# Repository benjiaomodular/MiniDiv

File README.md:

# MiniDiv
[![CC BY-SA 4.0][cc-by-sa-shield]][cc-by-sa]

A simple clock divider based on [HAGIWO's  design](https://note.com/solder_state/n/n7979cda44dcb).

## Schematics

Project sponsored by [PCBWay](https://pcbway.com).

See my full docs on my website: https://benjiaomodular.com/post/2024-11-22-minidiv-pcb/

## Versions
#### v0.3 - Fixed LED clearance issue
- To address LED clearance issues, I moved the LEDs to be mounted to the back, facing down, such that the LED shines through a hole on the board. 

#### v0.2 - Initial release
- First working version
- ISSUE: The LEDs were preventing the jacks from going in completly. The module still works but it might cause problems in the future.

## License

This work is licensed under a
[Creative Commons Attribution-ShareAlike 4.0 International License][cc-by-sa].

[![CC BY-SA 4.0][cc-by-sa-image]][cc-by-sa]

[cc-by-sa]: http://creativecommons.org/licenses/by-sa/4.0/
[cc-by-sa-image]: https://licensebuttons.net/l/by-sa/4.0/88x31.png
[cc-by-sa-shield]: https://img.shields.io/badge/License-CC%20BY--SA%204.0-lightgrey.svg

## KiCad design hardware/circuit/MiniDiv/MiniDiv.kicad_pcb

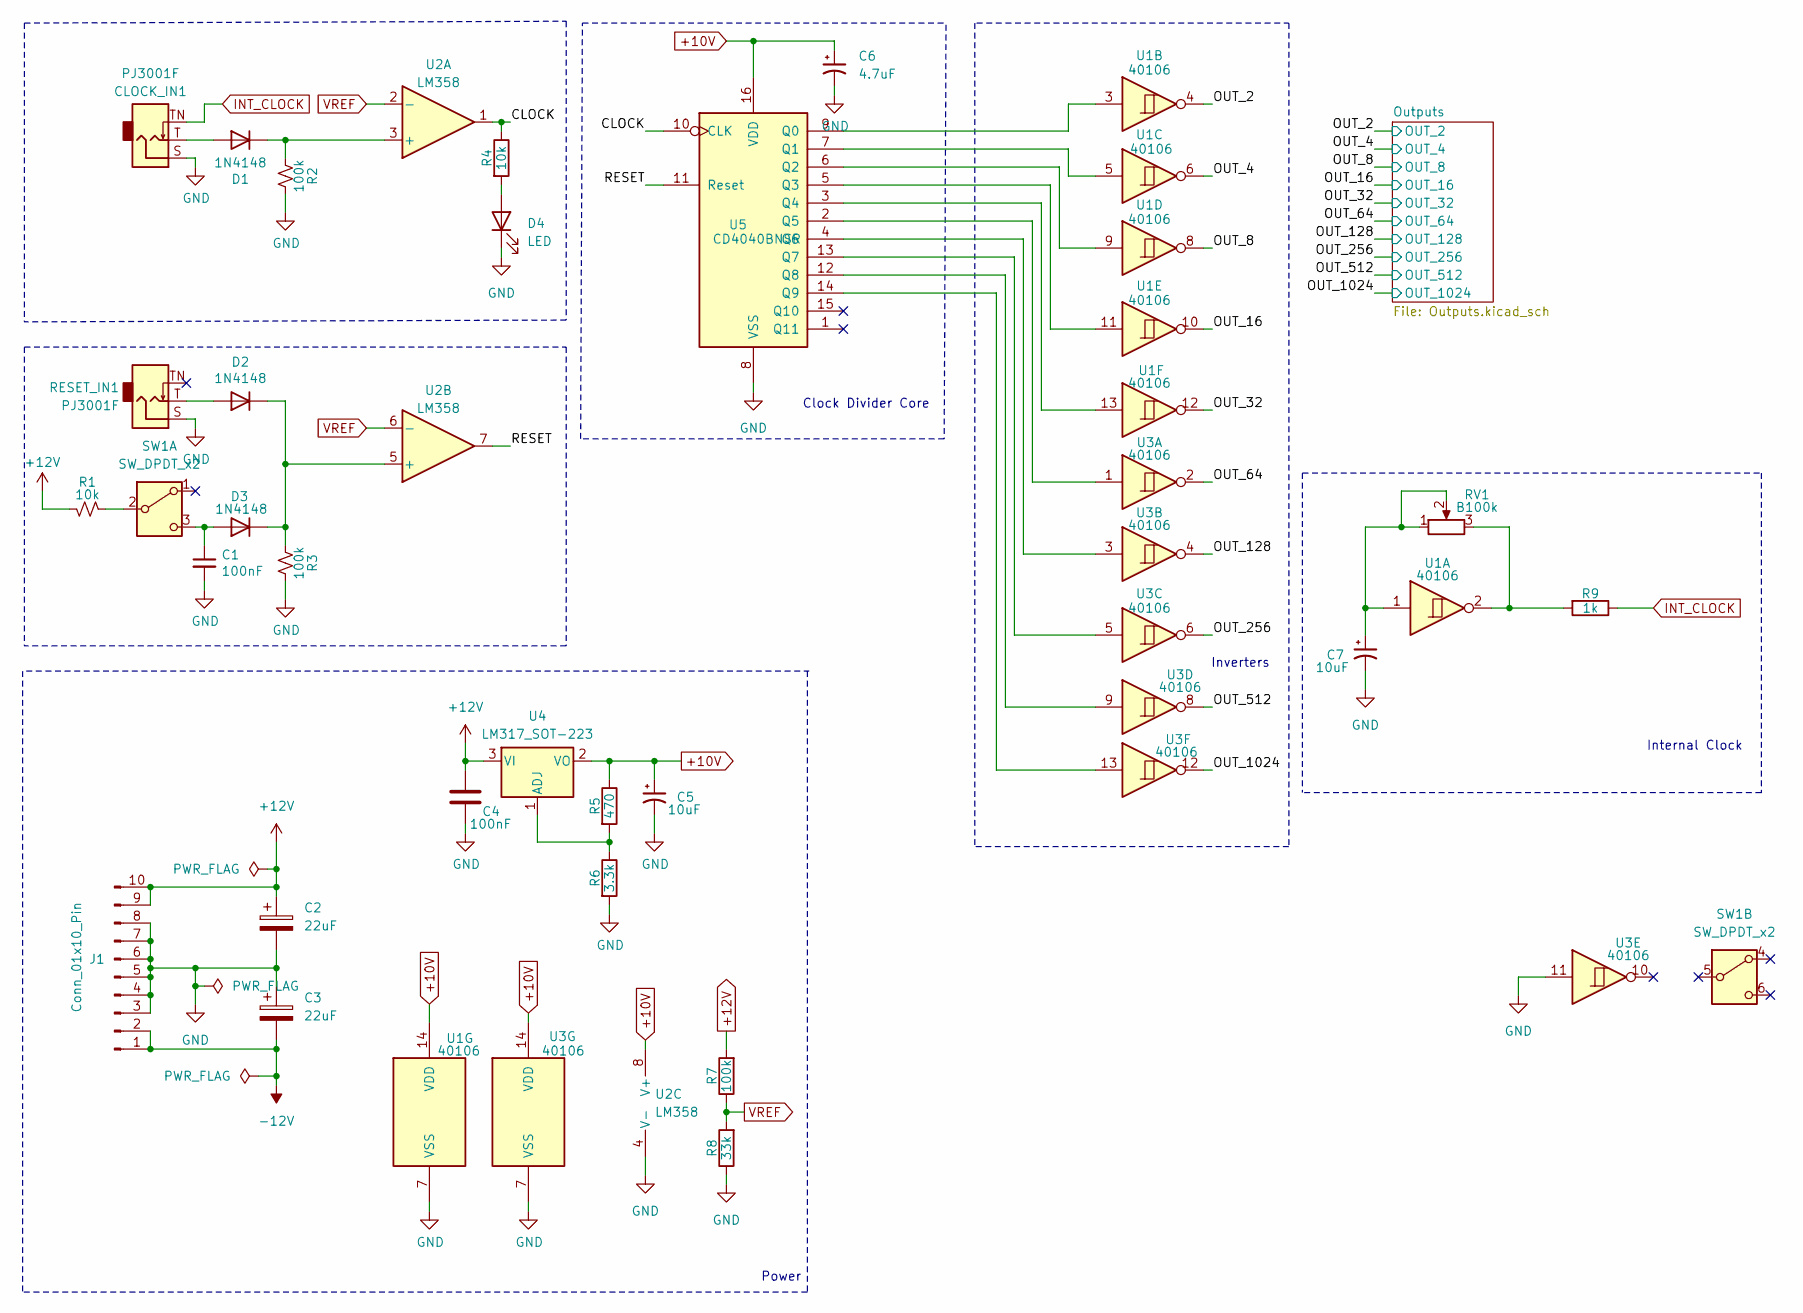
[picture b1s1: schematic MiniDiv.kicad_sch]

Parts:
C1: 100nF; C_0603_1608Metric_Pad1.08x0.95mm_HandSolder; Part # CC0805KRX7R9BB104
C2, C3: 22uF; CP_Elec_4x3.9; Part # EEE-FT1V220AR
C4: 100nF; C_0603_1608Metric_Pad1.08x0.95mm_HandSolder; Mfg # CC0603KRX7R8BB334; LCSC Part # C107070
C5, C7: 10uF; C_0805_2012Metric_Pad1.18x1.45mm_HandSolder; Part # TMK212BBJ106KG8T
C6: 4.7uF; C_0805_2012Metric_Pad1.18x1.45mm_HandSolder; Part # VJ0805G475KXQTW1BC
CLOCK_IN1: PJ3001F; AudioJack_3.5mm; Part # PJ-3001F
D1, D2, D3: 1N4148; D_SOD-123; Part # 1N4148WQ-7-F
D4: LED; LED_D3.0mm; Part # LED 3mm Orange
J1: Conn_01x10_Pin; Header_IDC2x05_NoArrow; Part # X9555WV-2X05-6TV01
R1, R4: 10k; R_0603_1608Metric_Pad0.98x0.95mm_HandSolder; Part # AC0603FR-0710KL
R2, R3, R7: 100k; R_0603_1608Metric_Pad0.98x0.95mm_HandSolder; Part # RC0603FR-07100KL
R5: 470; R_0603_1608Metric_Pad0.98x0.95mm_HandSolder; Part # RC0603FR-7W470RL
R6: 3.3k; R_0603_1608Metric_Pad0.98x0.95mm_HandSolder; Part # RC0603FR-7W3K3L
R8: 33k; R_0603_1608Metric_Pad0.98x0.95mm_HandSolder; Part # CR0603-FX-3302ELF
R9: 1k; R_0603_1608Metric_Pad0.98x0.95mm_HandSolder; Part # RC0603FR-071KL
RESET_IN1: PJ3001F; AudioJack_3.5mm; Part # PJ-3001F
RV1: B100k; Potentiometer_RV09; Part # RV09AF-40-20K-B100K
SW1: SW_DPDT_x2; Button_KFC7x7; Part # KFC7x7 Momentary
U1, U3: 40106; SOIC-14_3.9x8.7mm_P1.27mm; Part # Texas Instruments
U2: LM358; SOIC-8_5.23x5.23mm_P1.27mm; Part # Texas Instruments
U4: LM317_SOT-223; SOT-223-3_TabPin2; Part # Texas Instruments
U5: CD4040BNSR; SOIC-16W_5.3x10.2mm_P1.27mm; Part # Texas Instruments

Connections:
+10V: C5.1, C6.1, R5.1, U1.14 (VDD), U2.8 (V+), U3.14 (VDD), U4.2 (VO), U5.16 (VDD)
+12V: C2.1, C4.1, J1.9, J1.10, R1.1, R7.2, U4.3 (VI)
-12V: C3.2, J1.1, J1.2
/CLOCK: R4.1, U2.1, U5.10 (CLK)
/OUT_2: U1.4; also elsewhere on the board
/OUT_4: U1.6; also elsewhere on the board
/OUT_8: U1.8; also elsewhere on the board
/OUT_16: U1.10; also elsewhere on the board
/OUT_32: U1.12; also elsewhere on the board
/OUT_64: U3.2; also elsewhere on the board
/OUT_128: U3.4; also elsewhere on the board
/OUT_256: U3.6; also elsewhere on the board
/OUT_512: U3.8; also elsewhere on the board
/OUT_1024: U3.12; also elsewhere on the board
/RESET: U2.7, U5.11 (Reset)
GND: C1.2, C2.2, C3.1, C4.2, C5.2, C6.2, C7.2, CLOCK_IN1.S, D4.1 (K), J1.3, J1.4, J1.5, J1.6, J1.7, J1.8, R2.1, R3.1, R6.2, R8.1, RESET_IN1.S, U1.7 (VSS), U2.4 (V-), U3.7 (VSS), U3.11, U5.8 (VSS); also elsewhere on the board
INT_CLOCK: CLOCK_IN1.TN, R9.1
unnamed: C7.1, RV1.1, RV1.2, U1.1
unnamed: CLOCK_IN1.T, D1.2 (A)
unnamed: D1.1 (K), R2.2, U2.3 (+)
unnamed: D2.2 (A), RESET_IN1.T
unnamed: D2.1 (K), D3.1 (K), R3.2, U2.5 (+)
unnamed: C1.1, D3.2 (A), SW1.3 (C)
unnamed: D4.2 (A), R4.2
unnamed: R9.2, RV1.3, U1.2
unnamed: R1.2, SW1.2 (B)
unnamed: R5.2, R6.1, U4.1 (ADJ)
unnamed: U1.3, U5.9 (Q0)
unnamed: U1.5, U5.7 (Q1)
unnamed: U1.9, U5.6 (Q2)
unnamed: U1.11, U5.5 (Q3)
unnamed: U1.13, U5.3 (Q4)
unnamed: U3.1, U5.2 (Q5)
unnamed: U3.3, U5.4 (Q6)
unnamed: U3.5, U5.13 (Q7)
unnamed: U3.9, U5.12 (Q8)
unnamed: U3.13, U5.14 (Q9)
VREF: R7.1, R8.2, U2.2 (-), U2.6 (-)

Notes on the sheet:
Internal Clock
Clock Divider Core
Power
Inverters

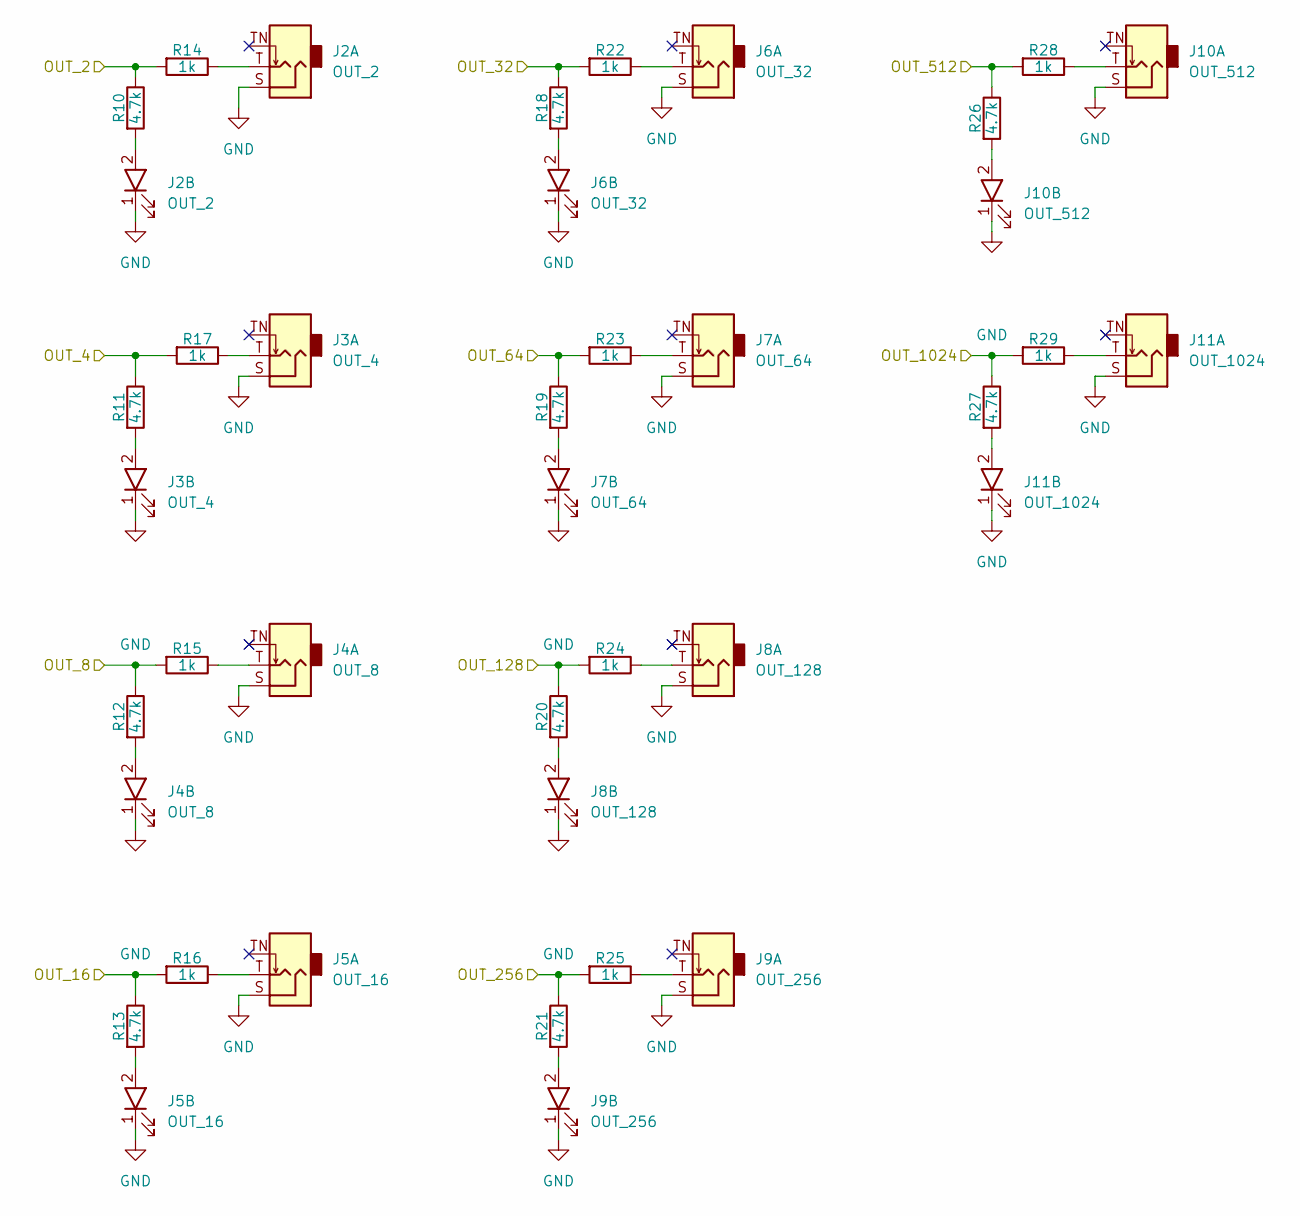
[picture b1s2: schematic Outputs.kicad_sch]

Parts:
J2: OUT_2; AudioJack_PJ3001F_0805LED
J3: OUT_4; AudioJack_PJ3001F_0805LED
J4: OUT_8; AudioJack_PJ3001F_0805LED
J5: OUT_16; AudioJack_PJ3001F_0805LED
J6: OUT_32; AudioJack_PJ3001F_0805LED
J7: OUT_64; AudioJack_PJ3001F_0805LED
J8: OUT_128; AudioJack_PJ3001F_0805LED
J9: OUT_256; AudioJack_PJ3001F_0805LED
J10: OUT_512; AudioJack_PJ3001F_0805LED
J11: OUT_1024; AudioJack_PJ3001F_0805LED
R10, R11, R12, R13, R18, R19, R20, R21, R26, R27: 4.7k; R_0603_1608Metric_Pad0.98x0.95mm_HandSolder; Part # RC0603FR-074K7L
R14, R15, R16, R17, R22, R23, R24, R25, R28, R29: 1k; R_0603_1608Metric_Pad0.98x0.95mm_HandSolder; Part # RC0603FR-071KL

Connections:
/OUT_2: R10.1, R14.2; also elsewhere on the board
/OUT_4: R11.1, R17.2; also elsewhere on the board
/OUT_8: R12.1, R15.2; also elsewhere on the board
/OUT_16: R13.1, R16.2; also elsewhere on the board
/OUT_32: R18.1, R22.2; also elsewhere on the board
/OUT_64: R19.1, R23.2; also elsewhere on the board
/OUT_128: R20.1, R24.2; also elsewhere on the board
/OUT_256: R21.1, R25.2; also elsewhere on the board
/OUT_512: R26.1, R28.2; also elsewhere on the board
/OUT_1024: R27.1, R29.2; also elsewhere on the board
GND: J2.1, J2.S, J3.1, J3.S, J4.1, J4.S, J5.1, J5.S, J6.1, J6.S, J7.1, J7.S, J8.1, J8.S, J9.1, J9.S, J10.1, J10.S, J11.1, J11.S; also elsewhere on the board
unnamed: J2.2, R10.2
unnamed: J2.T, R14.1
unnamed: J3.2, R11.2
unnamed: J3.T, R17.1
unnamed: J4.2, R12.2
unnamed: J4.T, R15.1
unnamed: J5.2, R13.2
unnamed: J5.T, R16.1
unnamed: J6.2, R18.2
unnamed: J6.T, R22.1
unnamed: J7.2, R19.2
unnamed: J7.T, R23.1
unnamed: J8.2, R20.2
unnamed: J8.T, R24.1
unnamed: J9.2, R21.2
unnamed: J9.T, R25.1
unnamed: J10.2, R26.2
unnamed: J10.T, R28.1
unnamed: J11.2, R27.2
unnamed: J11.T, R29.1

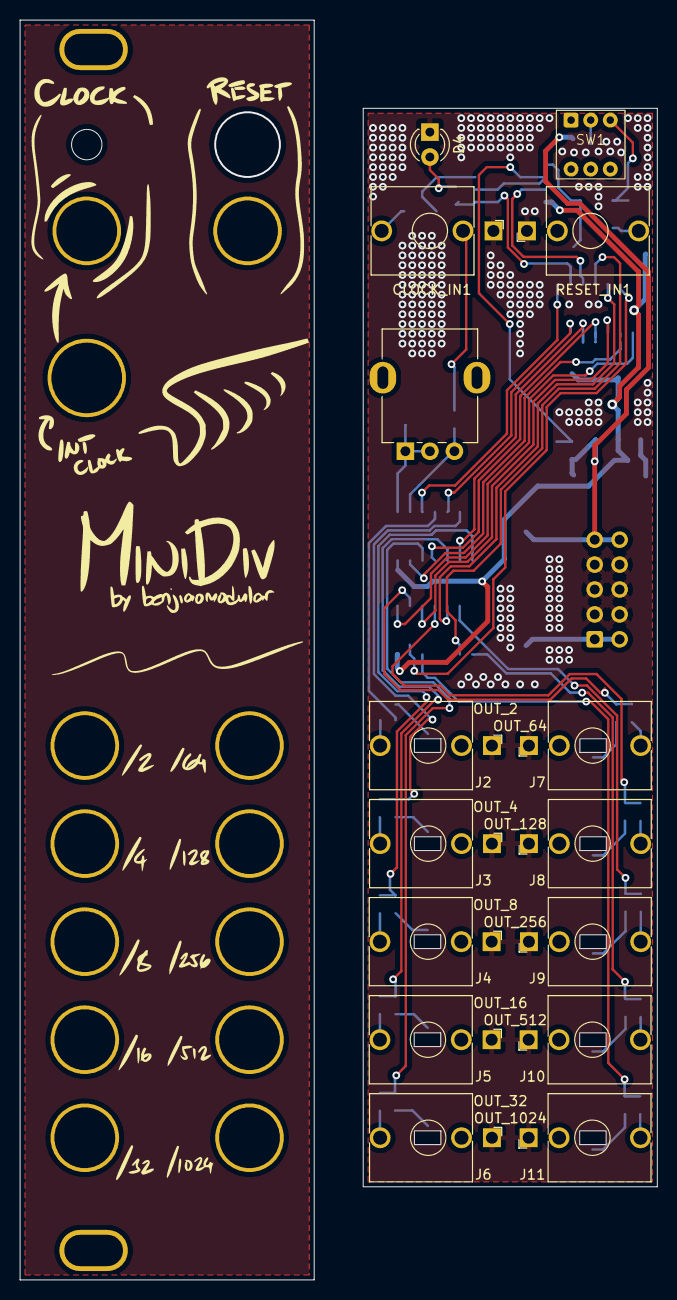
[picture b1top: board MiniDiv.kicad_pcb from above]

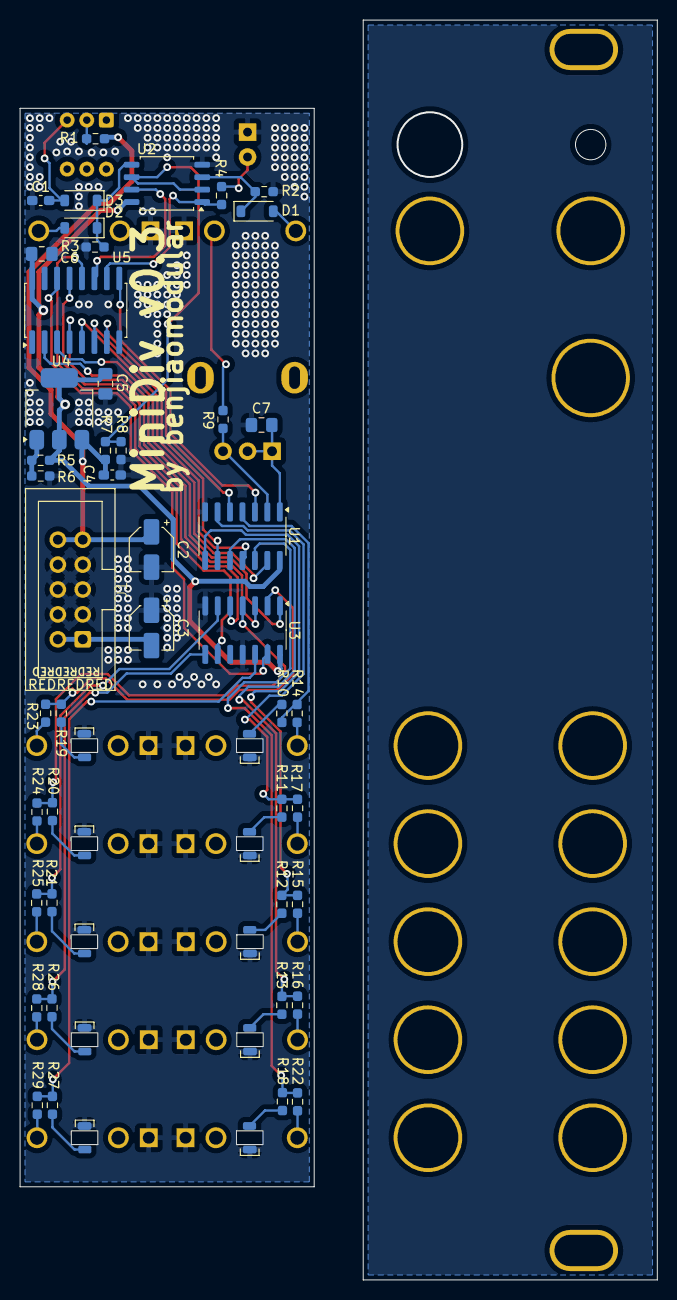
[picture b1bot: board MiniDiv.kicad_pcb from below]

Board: 2 copper layers, 30.0 x 110.0 mm, 60 parts (45 on the bottom side), 58 nets.

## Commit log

2023-05-26 Added schematics
2023-09-12 Updated schematics
2024-09-06 reorganized, updated license, finalized 0.2 circuit
2024-09-07 reorganized, schem ready for pcb
2024-09-11 v0.2 PCB
2024-10-28 Updated PCBs
2024-11-21 updated bom
2024-11-21 Added drawings and photos
2024-11-21 Fixed button to momentary
2024-11-25 Added version history
2025-08-17 Fixed LED clearance issues
2025-08-17 Added photos for minidiv
2025-09-13 Updated v0.3 BOMs
